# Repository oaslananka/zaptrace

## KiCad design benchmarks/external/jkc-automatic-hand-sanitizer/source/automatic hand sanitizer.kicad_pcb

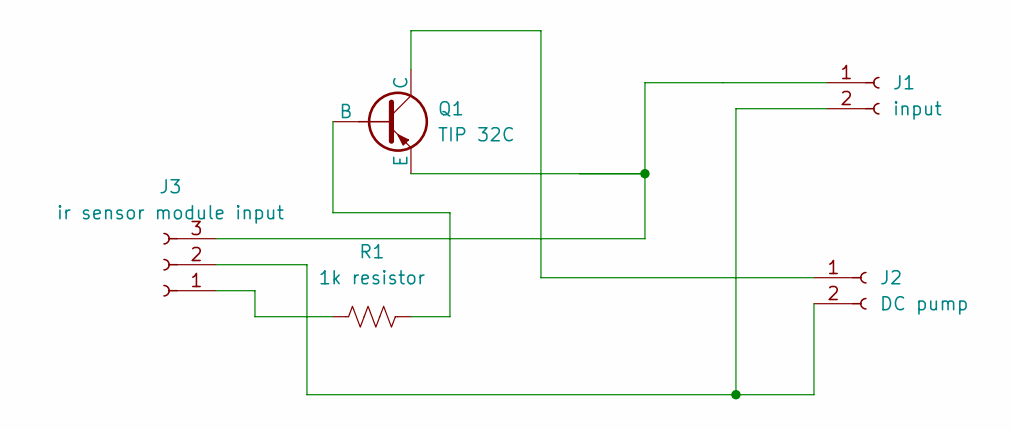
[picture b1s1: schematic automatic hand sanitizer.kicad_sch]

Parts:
J1: input; TerminalBlock_Phoenix_MKDS-1,5-2_1x02_P5.00mm_Horizontal
J2: DC pump; TerminalBlock_Phoenix_MKDS-1,5-2_1x02_P5.00mm_Horizontal
J3: ir sensor module input; TerminalBlock_Phoenix_MKDS-1,5-3-5.08_1x03_P5.08mm_Horizont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
Q1: TIP 32C; TO-220-3_Vertical
R1: 1k resistor; R_Axial_DIN0207_L6.3mm_D2.5mm_P7.62mm_Horizontal

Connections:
unnamed: J1.1, J3.3, Q1.3 (E)
unnamed: J1.2, J2.2, J3.2
unnamed: J2.1, Q1.1 (C)
unnamed: J3.1, R1.1
unnamed: Q1.2 (B), R1.2

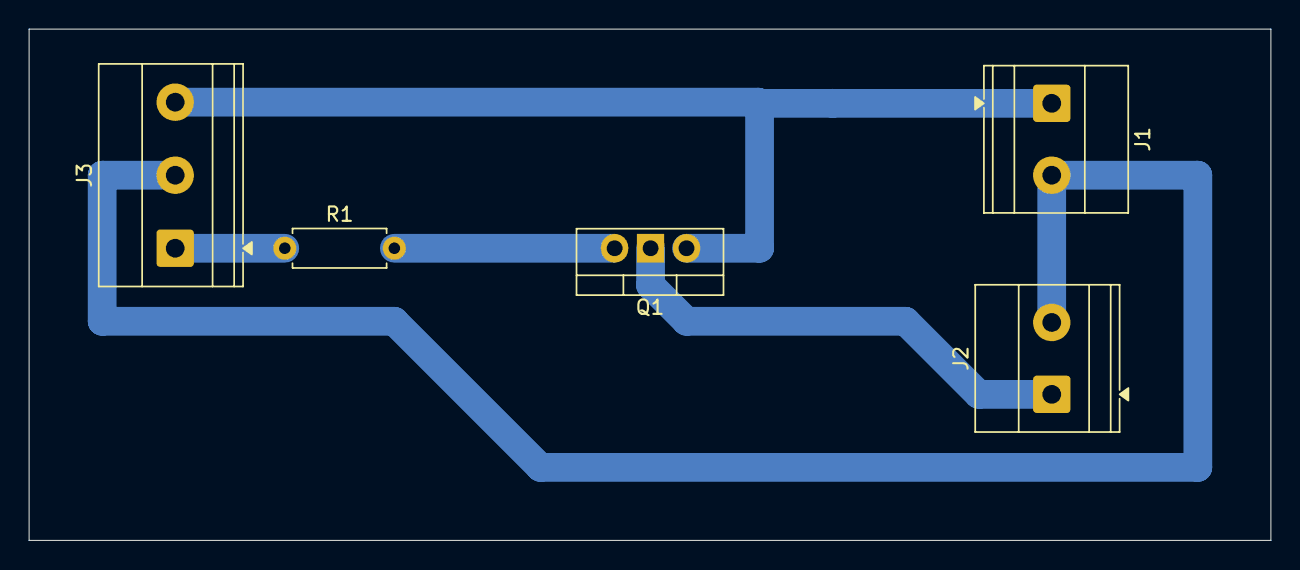
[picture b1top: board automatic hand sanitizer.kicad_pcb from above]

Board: 2 copper layers, 86.4 x 35.6 mm, 5 parts (0 on the bottom side), 5 nets.

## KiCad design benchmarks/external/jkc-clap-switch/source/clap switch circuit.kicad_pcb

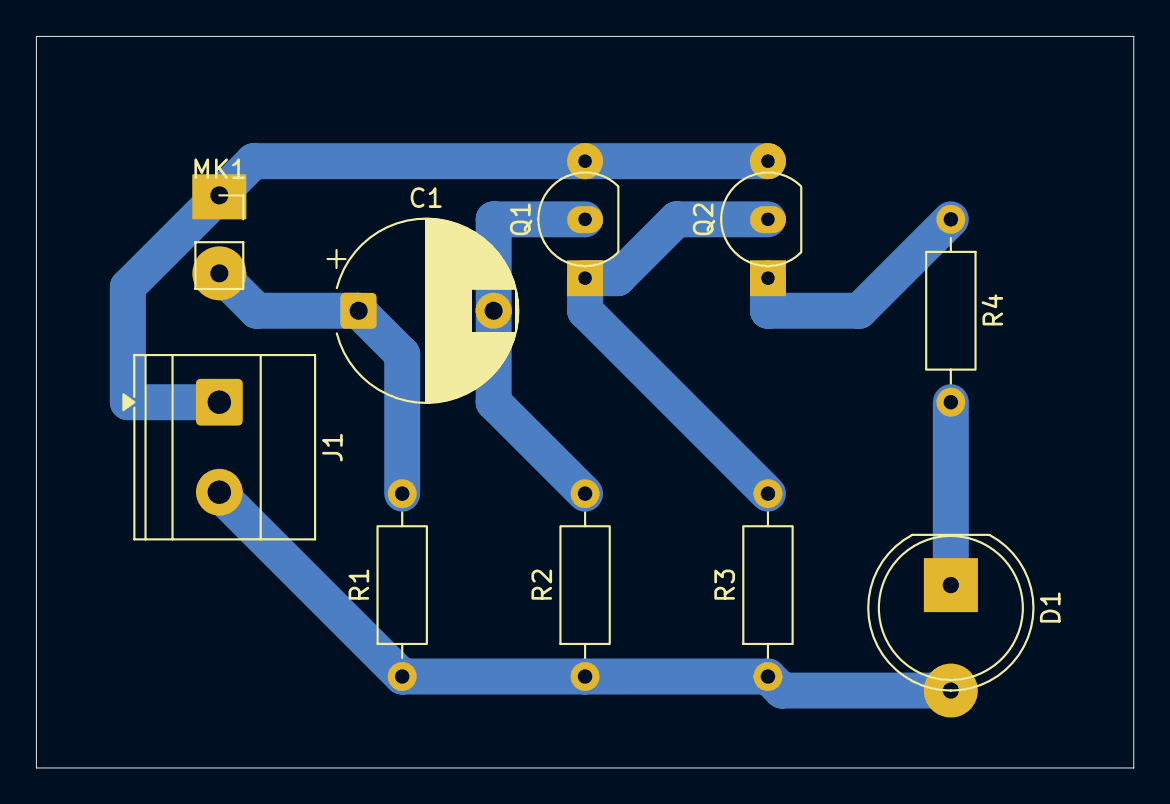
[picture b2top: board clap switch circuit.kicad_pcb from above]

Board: 2 copper layers, 61.0 x 40.6 mm, 10 parts (0 on the bottom side), 7 nets.

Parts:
C1: 47uf; CP_Radial_D10.0mm_P7.50mm
D1: LED; LED_D8.0mm
J1: input; TerminalBlock_Phoenix_MKDS-1,5-2_1x02_P5.00mm_Horizontal
MK1: Microphone_Condenser; PinSocket_1x02_P2.54mm_Vertical
Q1, Q2: BC547; TO-92_Inline
R1: 10k; R_Axial_DIN0207_L6.3mm_D2.5mm_P10.16mm_Horizontal
R2: 1m; R_Axial_DIN0207_L6.3mm_D2.5mm_P10.16mm_Horizontal
R3: 120k; R_Axial_DIN0207_L6.3mm_D2.5mm_P10.16mm_Horizontal
R4: 220; R_Axial_DIN0207_L6.3mm_D2.5mm_P10.16mm_Horizontal

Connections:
unnamed: D1.2 (A), J1.2, R1.1, R2.1, R3.1
unnamed: D1.1 (K), R4.2
unnamed: J1.1, MK1.1 (-), Q1.3 (E), Q2.3 (E)
unnamed: C1.1, MK1.2 (+), R1.2
unnamed: C1.2, Q1.2 (B), R2.2
unnamed: Q1.1 (C), Q2.2 (B), R3.2
unnamed: Q2.1 (C), R4.1

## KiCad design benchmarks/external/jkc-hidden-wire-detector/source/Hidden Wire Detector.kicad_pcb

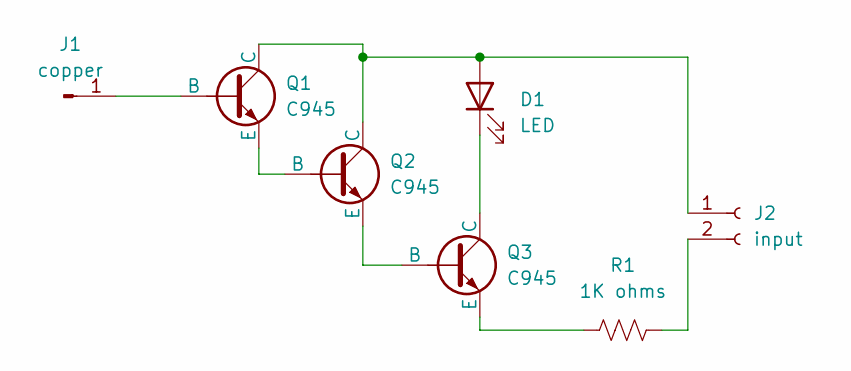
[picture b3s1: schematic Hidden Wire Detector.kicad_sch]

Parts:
D1: LED; LED_D5.0mm
J1: copper; PinHeader_1x01_P2.54mm_Horizontal
J2: input; TerminalBlock_Phoenix_MKDS-1,5-2_1x02_P5.00mm_Horizontal
Q1, Q2, Q3: C945; TO-220-3_Vertical
R1: 1K ohms; R_Axial_DIN0207_L6.3mm_D2.5mm_P7.62mm_Horizontal

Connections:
unnamed: D1.2 (A), J2.1, Q1.1 (C), Q2.1 (C)
unnamed: D1.1 (K), Q3.1 (C)
unnamed: J1.1 (Pin_1_1), Q1.2 (B)
unnamed: J2.2, R1.2
unnamed: Q1.3 (E), Q2.2 (B)
unnamed: Q2.3 (E), Q3.2 (B)
unnamed: Q3.3 (E), R1.1

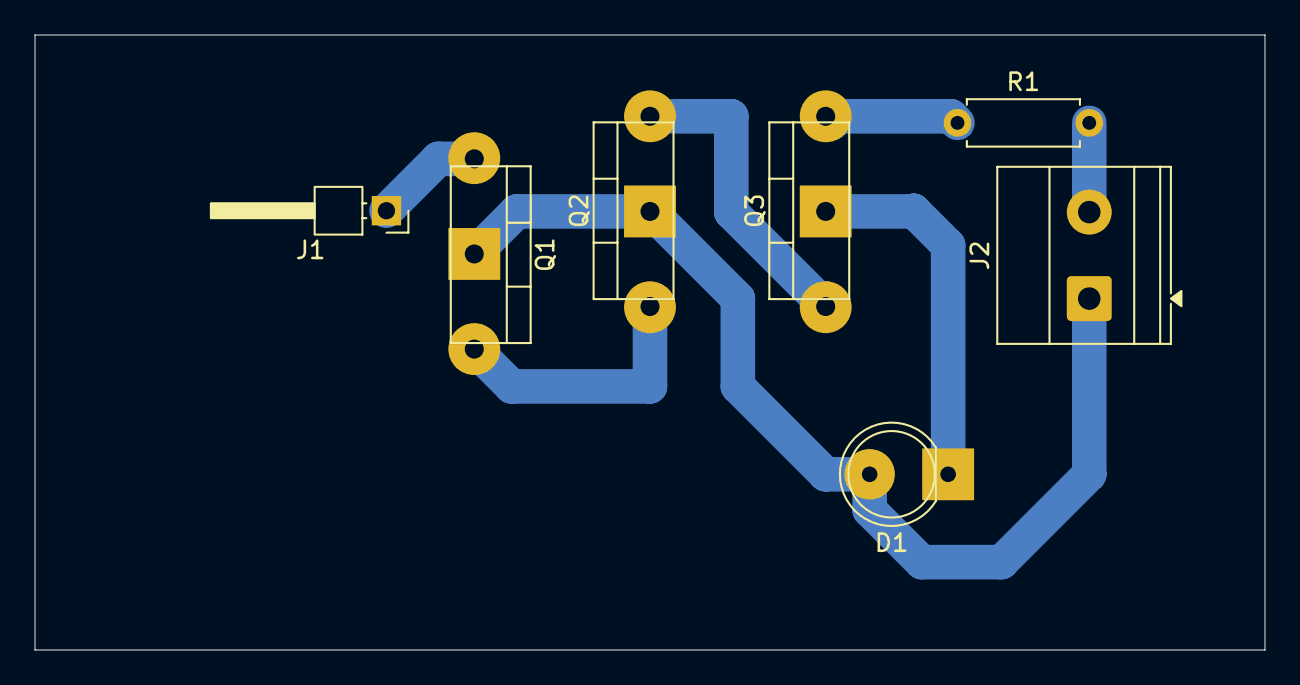
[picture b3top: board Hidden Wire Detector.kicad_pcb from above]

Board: 2 copper layers, 71.1 x 35.6 mm, 7 parts (0 on the bottom side), 7 nets.

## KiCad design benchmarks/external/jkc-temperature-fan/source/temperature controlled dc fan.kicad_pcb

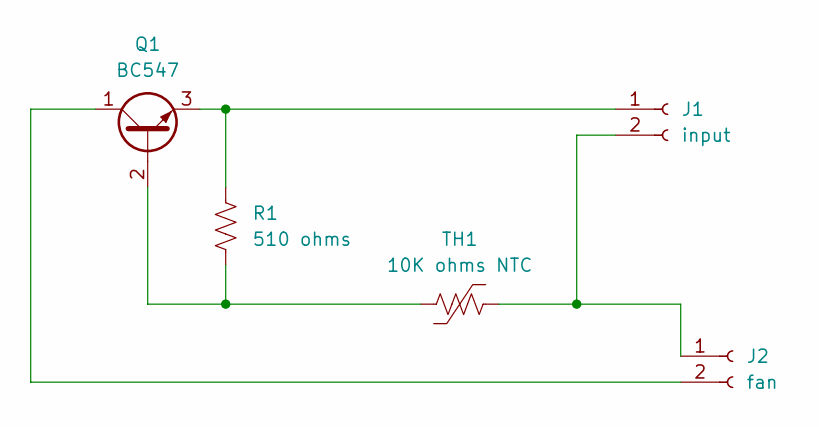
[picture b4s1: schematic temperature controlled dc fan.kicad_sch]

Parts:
J1: input; TerminalBlock_Phoenix_MKDS-1,5-2-5.08_1x02_P5.08mm_Horizont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
J2: fan; TerminalBlock_Phoenix_MKDS-1,5-2-5.08_1x02_P5.08mm_Horizont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
Q1: BC547; TO-92_Inline
R1: 510 ohms; R_Axial_DIN0207_L6.3mm_D2.5mm_P10.16mm_Horizontal
TH1: 10K ohms NTC; R_Axial_DIN0204_L3.6mm_D1.6mm_P5.08mm_Horizontal

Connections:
unnamed: J1.1, Q1.3 (E), R1.2
unnamed: J1.2, J2.1, TH1.1
unnamed: J2.2, Q1.1 (C)
unnamed: Q1.2 (B), R1.1, TH1.2

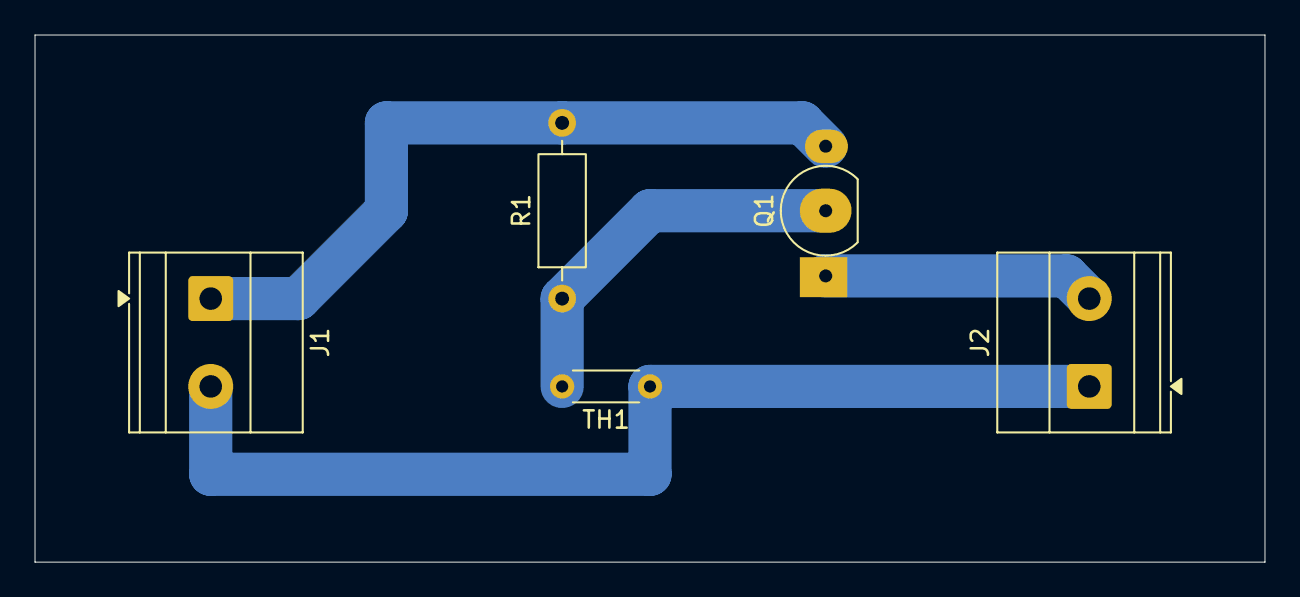
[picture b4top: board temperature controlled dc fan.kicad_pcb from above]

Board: 2 copper layers, 71.1 x 30.5 mm, 5 parts (0 on the bottom side), 4 nets.

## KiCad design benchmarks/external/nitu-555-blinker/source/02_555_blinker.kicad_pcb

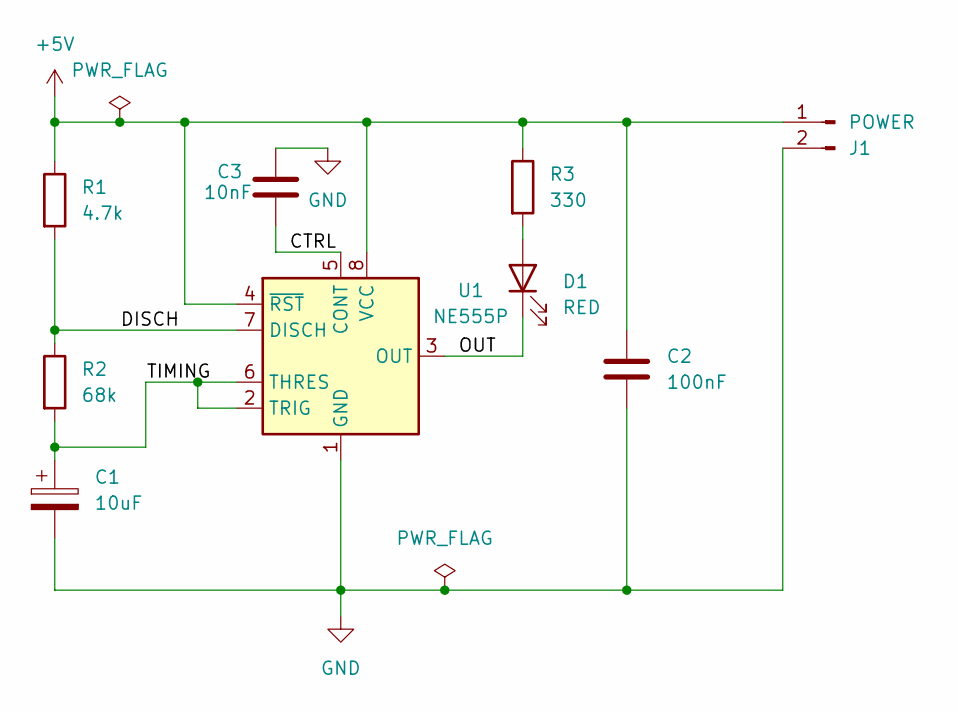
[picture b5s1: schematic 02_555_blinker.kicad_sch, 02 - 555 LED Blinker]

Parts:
C1: 10uF; CP_Radial_D5.0mm_P2.00mm
C2: 100nF; C_0805_2012Metric
C3: 10nF; C_0805_2012Metric
D1: RED; LED_0805_2012Metric
J1: POWER; PinHeader_1x02_P2.54mm_Vertical
R1: 4.7k; R_0805_2012Metric
R2: 68k; R_0805_2012Metric
R3: 330; R_0805_2012Metric
U1: NE555P; DIP-8_W7.62mm

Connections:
+5V: C2.1, J1.1, R1.1, R3.1, U1.4 (~RST), U1.8 (VCC)
/CTRL: C3.2, U1.5 (CONT)
/DISCH: R1.2, R2.1, U1.7 (DISCH)
/OUT: D1.1 (K), U1.3 (OUT)
/TIMING: C1.1, R2.2, U1.2 (TRIG), U1.6 (THRES)
GND: C1.2, C2.2, C3.1, J1.2, U1.1 (GND)
unnamed: D1.2 (A), R3.2

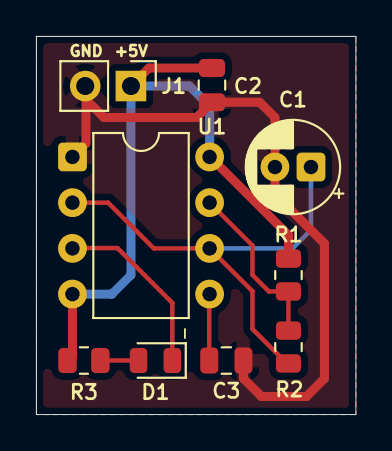
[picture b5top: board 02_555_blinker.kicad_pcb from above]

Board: 2 copper layers, 17.8 x 21.0 mm, 9 parts (0 on the bottom side), 7 nets.

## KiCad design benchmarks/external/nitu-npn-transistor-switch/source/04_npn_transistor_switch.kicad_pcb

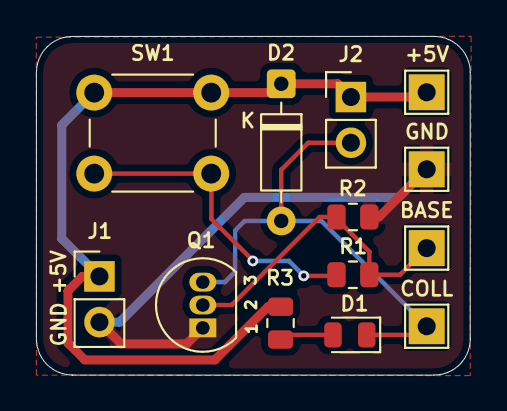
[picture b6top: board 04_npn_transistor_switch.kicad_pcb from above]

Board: 2 copper layers, 24.1 x 18.8 mm, 13 parts (0 on the bottom side), 6 nets.

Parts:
+5V: +5V; TestPoint_THTPad_2.0x2.0mm_Drill1.0mm
BASE: BASE; TestPoint_THTPad_2.0x2.0mm_Drill1.0mm
COLL: COLL; TestPoint_THTPad_2.0x2.0mm_Drill1.0mm
D1: RED; LED_0805_2012Metric
D2: 1N4148; D_DO-35_SOD27_P7.62mm_Horizontal
GND: GND; TestPoint_THTPad_2.0x2.0mm_Drill1.0mm
J1: POWER; PinHeader_1x02_P2.54mm_Vertical
J2: LOAD; PinHeader_1x02_P2.54mm_Vertical
Q1: PN2222A; TO-92_Inline
R1: 390; R_0805_2012Metric
R2: 10k; R_0805_2012Metric
R3: 330; R_0805_2012Metric
SW1: SW_Push; SW_PUSH_6mm

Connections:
+5V: +5V.1 (1_1), D2.1 (K), J1.1, J2.1, R3.1, SW1.1
GND: GND.1 (1_1), J1.2, Q1.1 (E), R2.2
unnamed: D1.2 (A), R3.2
unnamed: COLL.1 (1_1), D1.1 (K), D2.2 (A), J2.2, Q1.3 (C)
unnamed: BASE.1 (1_1), Q1.2 (B), R1.2, R2.1
unnamed: R1.1, SW1.2

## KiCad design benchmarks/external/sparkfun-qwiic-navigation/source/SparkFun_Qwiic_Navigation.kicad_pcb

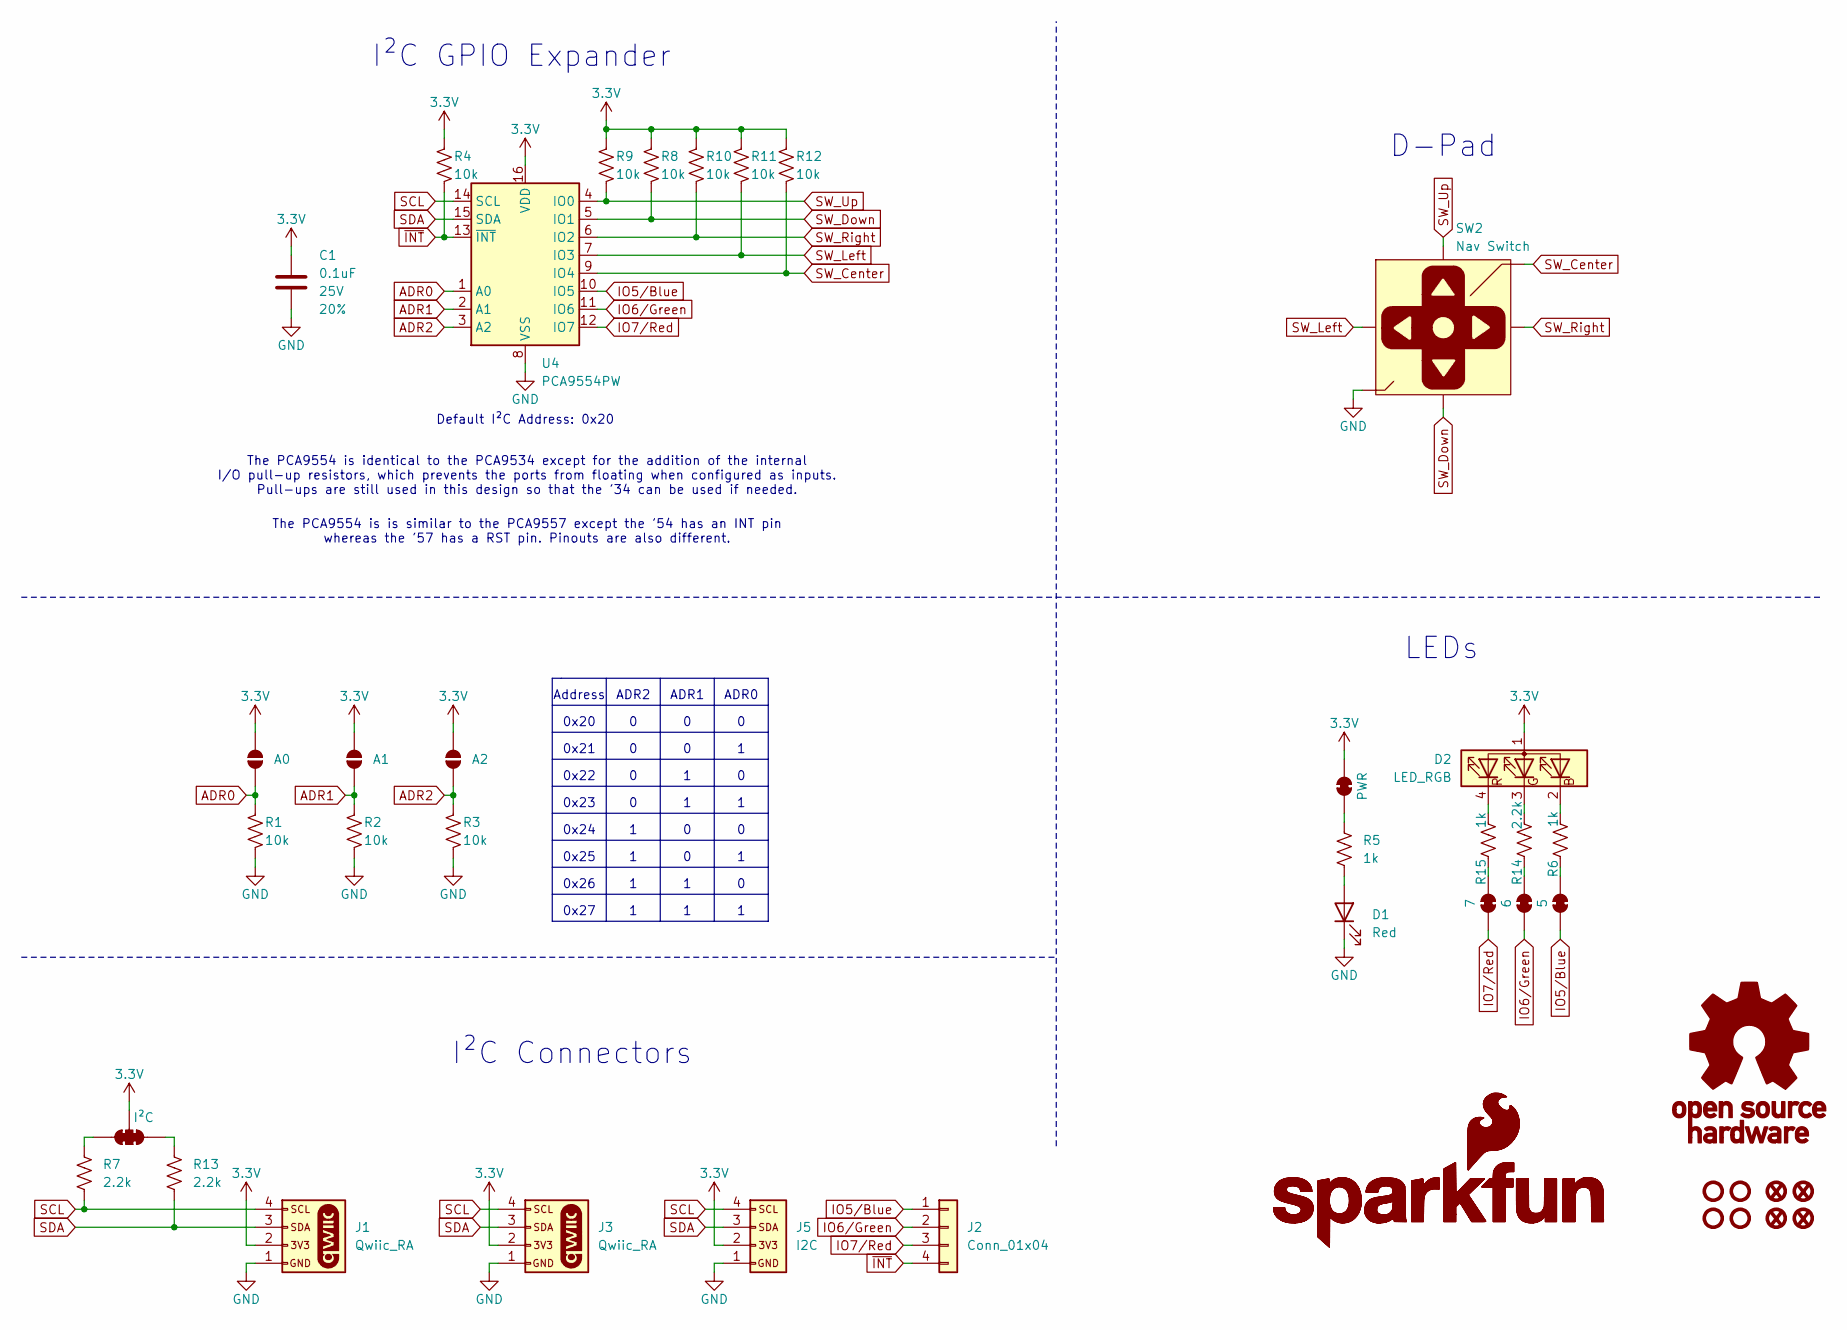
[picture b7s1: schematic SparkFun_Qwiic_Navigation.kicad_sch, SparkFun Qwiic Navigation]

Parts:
C1: 0.1uF; C_0603_1608Metric; Voltage 25V; Tolerance 20%
D1: Red; LED_0603_1608Metric_Red
D2: LED_RGB; LED_1205_RGB_Bottom
FID1, FID2, FID3, FID4: Fiducial_0.5mm; Fiducial_0.5mm_Mask1mm
G1: OSHW_Logo; Creative_Commons_License
G3: SparkFun_Logo
G5: SparkFun_Logo; SparkFun_Logo_8mm
J1, J3: Qwiic_RA; JST_SMD_1.0mm-4_RA
J2: Conn_01x04; 1x04
J5: I2C; 1x04
JP1: A0; Jumper_2_NO
JP2: A1; Jumper_2_NO
JP3: A2; Jumper_2_NO
JP4: PWR; Jumper_2_NC_Trace
JP5: 5; Jumper_2_NC_Trace
JP6: I²C; Jumper_3_NC-2_Trace
JP7: 6; Jumper_2_NC_Trace
JP8: 7; Jumper_2_NC_Trace
R1, R2, R3, R4, R8, R9, R10, R11, R12: 10k; R_0603_1608Metric
R5, R6, R15: 1k; R_0603_1608Metric
R7, R13, R14: 2.2k; R_0603_1608Metric
ST1, ST2, ST3, ST4: Standoff
SW2: Nav Switch; Navigation_SMD_7.5x7.5mm
U4: PCA9554PW; TSSOP-16_4.4x5mm_P0.65mm

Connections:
3.3V: C1.1, D2.1 (A), J1.2, J3.2, J5.2, JP1.2 (B), JP2.2 (B), JP3.2 (B), JP4.2 (B), JP6.2 (C), R4.2, R8.2, R9.2, R10.2, R11.2, R12.2, U4.16 (VDD)
ADR0: JP1.1 (A), R1.2, U4.1 (A0)
ADR1: JP2.1 (A), R2.2, U4.2 (A1)
ADR2: JP3.1 (A), R3.2, U4.3 (A2)
GND: C1.2, D1.1 (K), J1.1, J3.1, J5.1, R1.1, R2.1, R3.1, SW2.2 (GND), U4.8 (VSS)
IO5/Blue: J2.1, JP5.2 (B), U4.10 (IO5)
IO6/Green: J2.2, JP7.2 (B), U4.11 (IO6)
IO7/Red: J2.3, JP8.2 (B), U4.12 (IO7)
unnamed: D1.2 (A), R5.2
unnamed: D2.2 (BK), R6.2
unnamed: D2.3 (GK), R14.2
unnamed: D2.4 (RK), R15.2
unnamed: JP4.1 (A), R5.1
unnamed: JP5.1 (A), R6.1
unnamed: JP6.1 (A), R13.1
unnamed: JP6.3 (B), R7.1
unnamed: JP7.1 (A), R14.1
unnamed: JP8.1 (A), R15.1
SCL: J1.4, J3.4, J5.4, R7.2, U4.14 (SCL)
SDA: J1.3, J3.3, J5.3, R13.2, U4.15 (SDA)
SW_Center: R12.1, SW2.5 (Center), U4.9 (IO4)
SW_Down: R8.1, SW2.3 (Down), U4.5 (IO1)
SW_Left: R11.1, SW2.1 (Left), U4.7 (IO3)
SW_Right: R10.1, SW2.4 (Right), U4.6 (IO2)
SW_Up: R9.1, SW2.6 (Up), U4.4 (IO0)
~INT: J2.4, R4.1, U4.13 (~INT)

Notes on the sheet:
The PCA9554 is is similar to the PCA9557 except the '54 has an INT pin whereas the '57 has a RST pin. Pinouts are also different.
Default I²C Address: 0x20
I²C GPIO Expander
0x20
I²C Connectors
ADR2
ADR0
0x23
The PCA9554 is identical to the PCA9534 except for the addition of the internal I/O pull-up resistors, which prevents the ports from floating when configured as inputs. Pull-ups are still used in this design so that the '34 can be used if needed.
0x22
LEDs
0x25
0x26
0x24
D-Pad
0x27
ADR1
0x21
Address

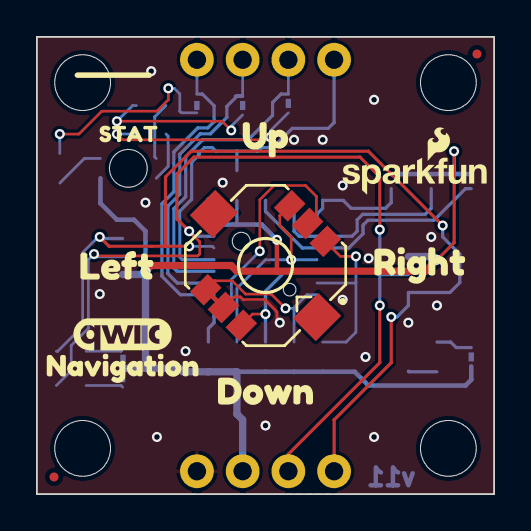
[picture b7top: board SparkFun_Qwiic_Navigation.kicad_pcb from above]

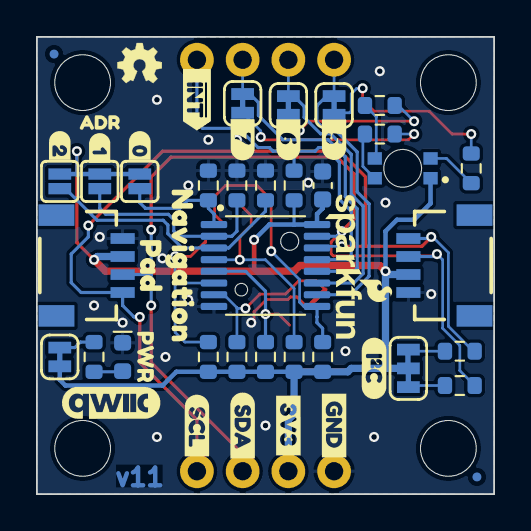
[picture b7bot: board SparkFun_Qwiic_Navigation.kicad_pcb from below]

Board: 2 copper layers, 25.4 x 25.4 mm, 64 parts (48 on the bottom side), 26 nets.

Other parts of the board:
Ref**: Val**; OSHW_Logo_2.5mm
kibuzzard-64C2E6A3: G***; kibuzzard-64C2E6A3
kibuzzard-66EED5D2: G***; kibuzzard-66EED5D2
kibuzzard-66EF6B89: G***; kibuzzard-66EF6B89
kibuzzard-66EF7A0B: G***; kibuzzard-66EF7A0B
kibuzzard-66EF7A03: G***; kibuzzard-66EF7A03
kibuzzard-66EF7A24: G***; kibuzzard-66EF7A24
kibuzzard-66EF7AE6: G***; kibuzzard-66EF7AE6
kibuzzard-66EF7AEF: G***; kibuzzard-66EF7AEF
kibuzzard-66EF7B1E: G***; kibuzzard-66EF7B1E
kibuzzard-66EF7B7C: G***; kibuzzard-66EF7B7C
kibuzzard-66EF7B15: G***; kibuzzard-66EF7B15
kibuzzard-66EF55AC: G***; kibuzzard-66EF55AC
kibuzzard-66EF79E9: G***; kibuzzard-66EF79E9
kibuzzard-66EF559E: G***; kibuzzard-66EF559E
kibuzzard-66EF5597: G***; kibuzzard-66EF5597
kibuzzard-66F18F5E: G***; kibuzzard-66F18F5E
kibuzzard-66F18F8F: G***; kibuzzard-66F18F8F
kibuzzard-66F18F9B: G***; kibuzzard-66F18F9B
kibuzzard-66F182A6: G***; kibuzzard-66F182A6
kibuzzard-675B45F7: G***; kibuzzard-675B45F7
kibuzzard-67117BDD: G***; kibuzzard-67117BDD
kibuzzard-6730262A: G***; kibuzzard-6730262A

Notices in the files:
benchmarks/external/nitu-555-blinker/source/02_555_blinker.kicad_pcb:
©NITISH GHADAGE
parts and their libraries:
https://creativecommons.org/licenses/by-sa/4.0
Released under the Creative Commons Attribution Share-Alike 4.0 License
